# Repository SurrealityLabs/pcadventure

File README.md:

# pcadventure
Adventures in PC Hardware. Probably rather expensive.

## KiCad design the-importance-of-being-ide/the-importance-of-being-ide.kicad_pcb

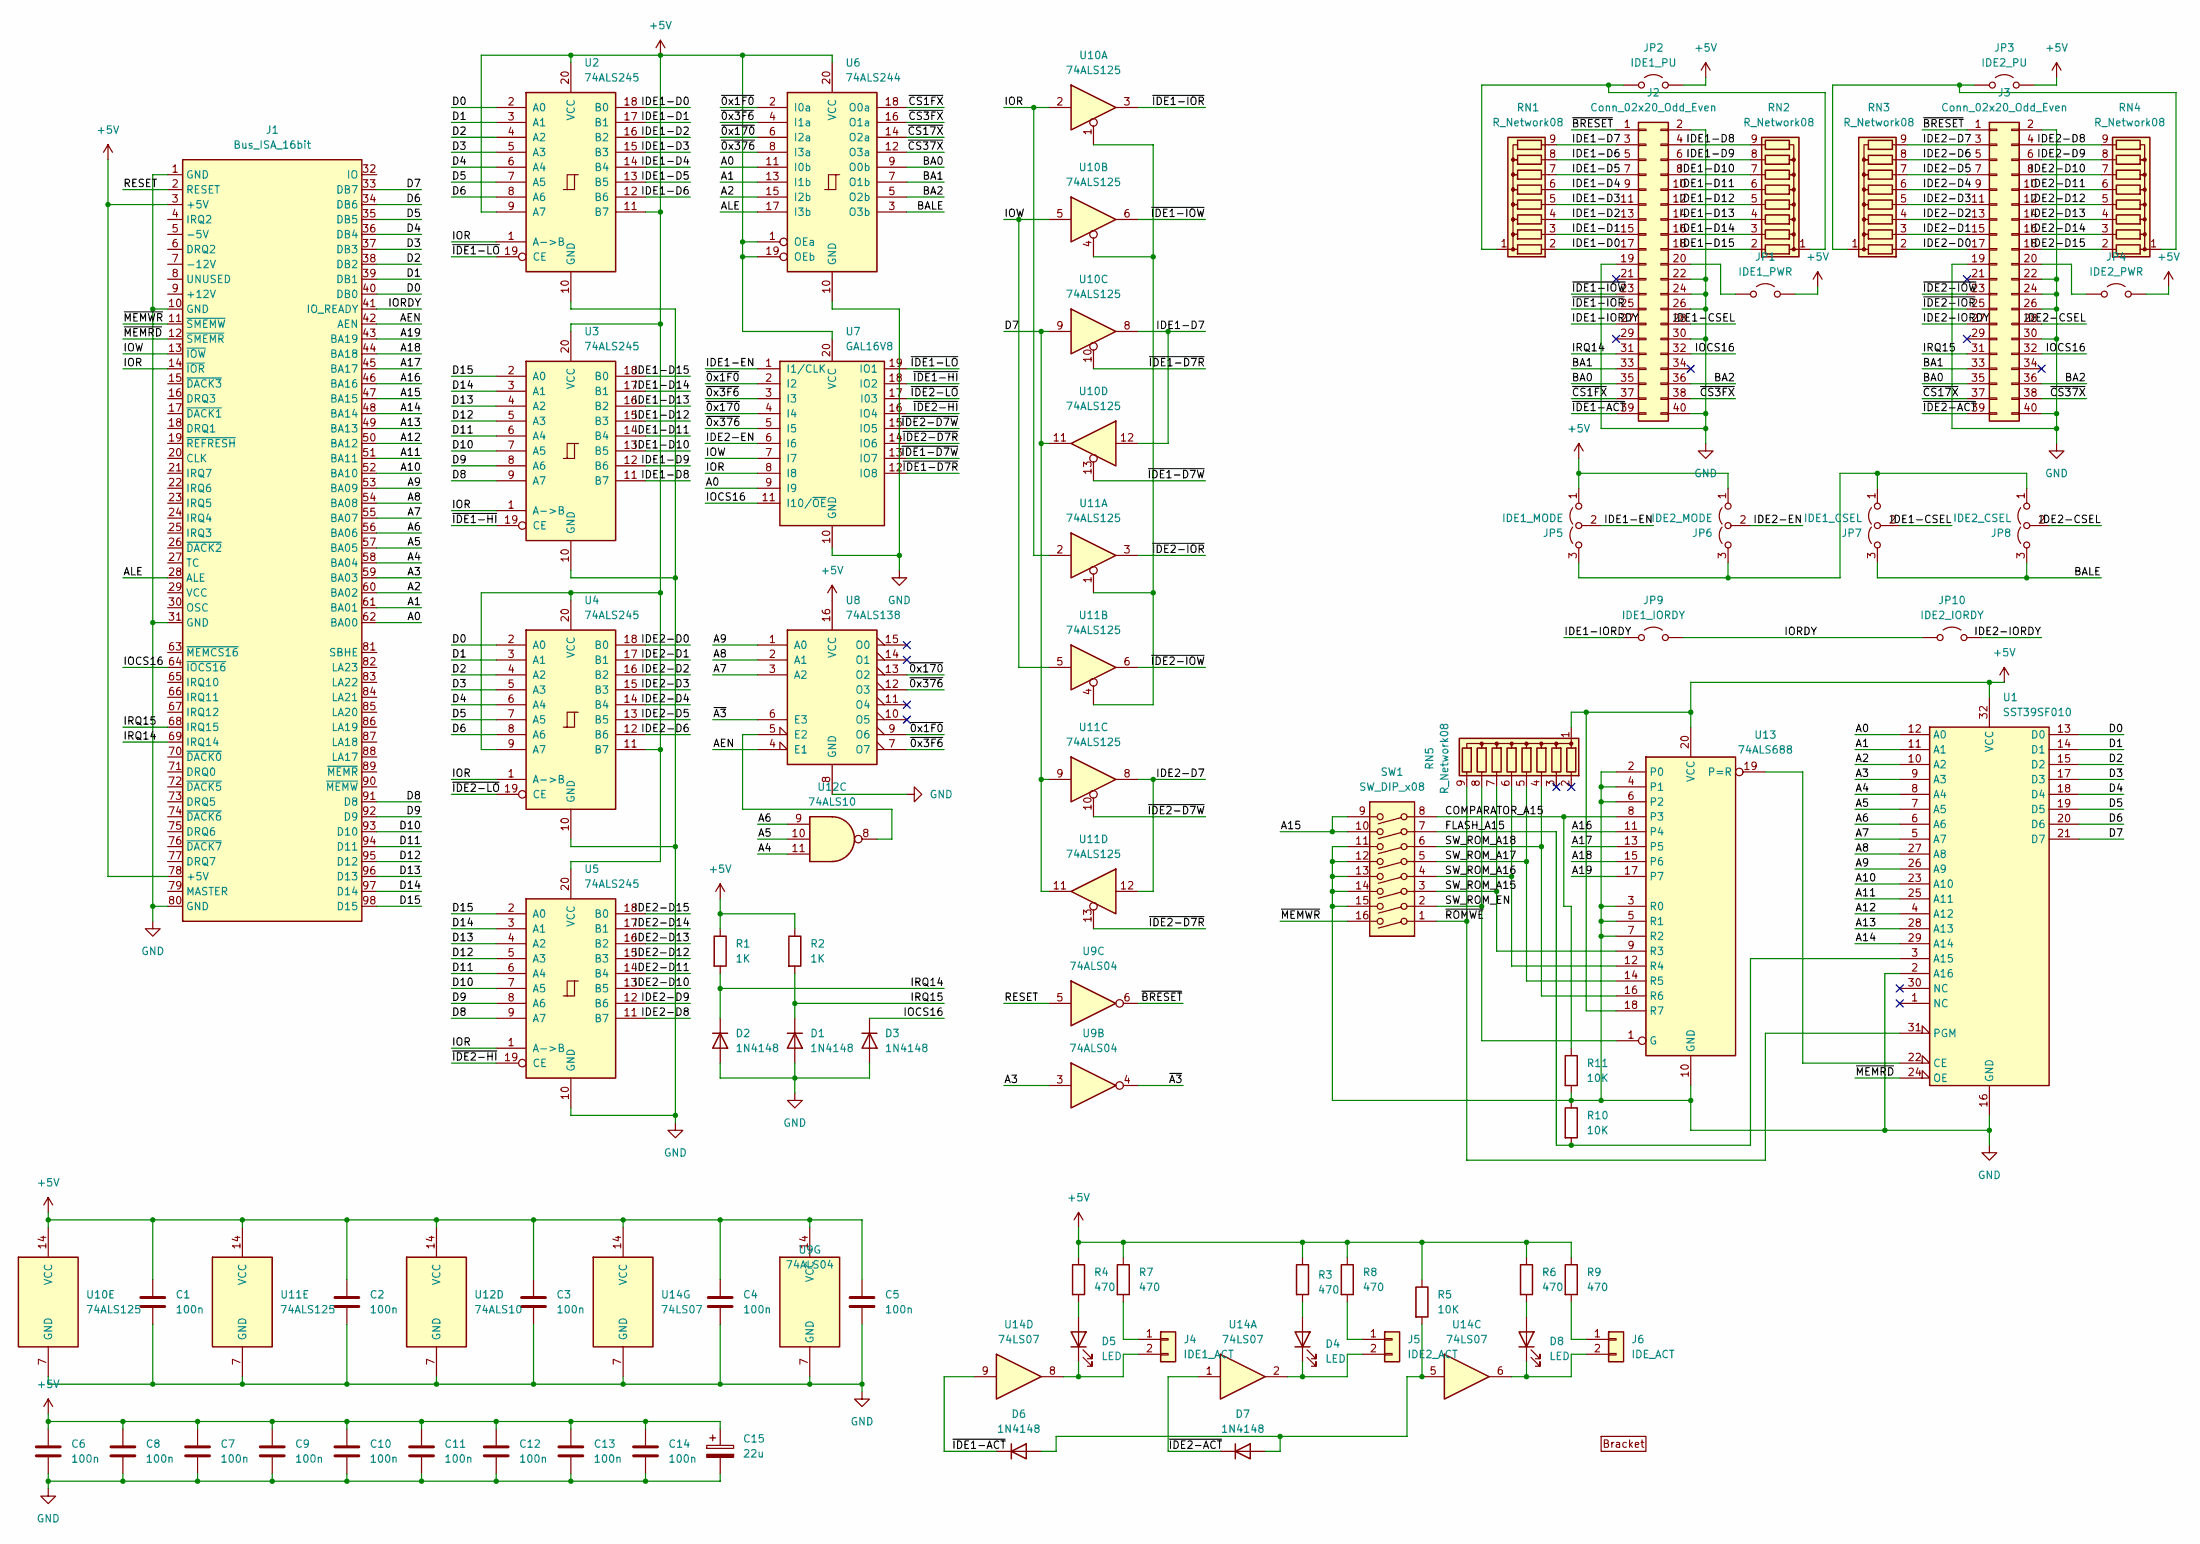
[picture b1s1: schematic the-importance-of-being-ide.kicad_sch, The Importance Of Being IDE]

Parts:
BRACKET1: PC_BRACKET_ISA_KEYSTONE_9202_Rev1
C1, C2, C3, C4, C5, C6, C7, C8, C9, C10, C11, C12, C13, C14: 100n; C_0603_1608Metric_Pad1.08x0.95mm_HandSolder
C15: 22u; CP_Elec_5x5.3
D1, D2, D3, D6, D7: 1N4148; D_SOD-123
D4, D5, D8: LED; LED_0603_1608Metric_Pad1.05x0.95mm_HandSolder
J1: Bus_ISA_16bit; BUS_AT
J2, J3: Conn_02x20_Odd_Even; IDC-Header_2x20_P2.54mm_Vertical
J4: IDE1_ACT; Molex_KK-254_AE-6410-02A_1x02_P2.54mm_Vertical
J5: IDE2_ACT; Molex_KK-254_AE-6410-02A_1x02_P2.54mm_Vertical
J6: IDE_ACT; Molex_KK-254_AE-6410-02A_1x02_P2.54mm_Vertical
JP1: IDE1_PWR; PinHeader_1x02_P2.54mm_Vertical
JP2: IDE1_PU; PinHeader_1x02_P2.54mm_Vertical
JP3: IDE2_PU; PinHeader_1x02_P2.54mm_Vertical
JP4: IDE2_PWR; PinHeader_1x02_P2.54mm_Vertical
JP5: IDE1_MODE; PinHeader_1x03_P2.54mm_Vertical
JP6: IDE2_MODE; PinHeader_1x03_P2.54mm_Vertical
JP7: IDE1_CSEL; PinHeader_1x03_P2.54mm_Vertical
JP8: IDE2_CSEL; PinHeader_1x03_P2.54mm_Vertical
JP9: IDE1_IORDY; PinHeader_1x02_P2.54mm_Vertical
JP10: IDE2_IORDY; PinHeader_1x02_P2.54mm_Vertical
R1, R2: 1K; R_0603_1608Metric_Pad0.98x0.95mm_HandSolder
R3, R4, R6, R7, R8, R9: 470; R_0603_1608Metric_Pad0.98x0.95mm_HandSolder
R5, R10, R11: 10K; R_0603_1608Metric_Pad0.98x0.95mm_HandSolder
RN1, RN2, RN3, RN4, RN5: R_Network08; R_Array_SIP9
SW1: SW_DIP_x08; SW_DIP_SPSTx08_Slide_9.78x22.5mm_W7.62mm_P2.54mm
U1: SST39SF010; DIP-32_W15.24mm
U2, U3, U4, U5: 74ALS245; DIP-20_W7.62mm
U6: 74ALS244; DIP-20_W7.62mm
U7: GAL16V8; DIP-20_W7.62mm
U8: 74ALS138; DIP-16_W7.62mm
U9: 74ALS04; DIP-14_W7.62mm
U10, U11: 74ALS125; DIP-14_W7.62mm
U12: 74ALS10; DIP-14_W7.62mm
U13: 74ALS688; DIP-20_W7.62mm
U14: 74LS07; DIP-14_W7.62mm

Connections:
+5V: C1.1, C2.1, C3.1, C4.1, C5.1, C6.1, C7.1, C8.1, C9.1, C10.1, C11.1, C12.1, C13.1, C14.1, C15.1, J1.3 (+5V), J1.78 (+5V), JP1.2 (B), JP2.2 (B), JP3.2 (B), JP4.2 (B), JP5.1 (A), JP6.1 (A), R1.1, R2.1, R3.1, R4.1, R5.1, R6.1, R7.1, R8.1, R9.1, RN5.1 (common), U1.32 (VCC), U2.9 (A7), U2.11 (B7), U2.20 (VCC), U3.20 (VCC), U4.9 (A7), U4.11 (B7), U4.20 (VCC), U5.20 (VCC), U6.1 (OEa), U6.19 (OEb), U6.20 (VCC), U7.20 (VCC), U8.16 (VCC), U9.14 (VCC), U10.14 (VCC), U11.14 (VCC), U12.14 (VCC), U13.18 (R7), U13.20 (VCC), U14.14 (VCC)
/A0: J1.62 (BA00), U1.12 (A0), U6.11 (I0b), U7.9 (I9)
/A1: J1.61 (BA01), U1.11 (A1), U6.13 (I1b)
/A2: J1.60 (BA02), U1.10 (A2), U6.15 (I2b)
/A3: J1.59 (BA03), U1.9 (A3), U9.3
/A4: J1.58 (BA04), U1.8 (A4), U12.11
/A5: J1.57 (BA05), U1.7 (A5), U12.10
/A6: J1.56 (BA06), U1.6 (A6), U12.9
/A7: J1.55 (BA07), U1.5 (A7), U8.3 (A2)
/A8: J1.54 (BA08), U1.27 (A8), U8.2 (A1)
/A9: J1.53 (BA09), U1.26 (A9), U8.1 (A0)
/A10: J1.52 (BA10), U1.23 (A10)
/A11: J1.51 (BA11), U1.25 (A11)
/A12: J1.50 (BA12), U1.4 (A12)
/A13: J1.49 (BA13), U1.28 (A13)
/A14: J1.48 (BA14), U1.29 (A14)
/A15: J1.47 (BA15), SW1.9, SW1.10
/A16: J1.46 (BA16), U13.11 (P4)
/A17: J1.45 (BA17), U13.13 (P5)
/A18: J1.44 (BA18), U13.15 (P6)
/A19: J1.43 (BA19), U13.17 (P7)
/AEN: J1.42 (AEN), U8.4 (E1)
/ALE: J1.28 (ALE), U6.17 (I3b)
/BA0: J2.35, J3.35, U6.9 (O0b)
/BA1: J2.33, J3.33, U6.7 (O1b)
/BA2: J2.36, J3.36, U6.5 (O2b)
/BALE: JP7.3 (B), JP8.3 (B), U6.3 (O3b)
/COMPARATOR_A15: R11.1, SW1.8, U13.8 (P3)
/D0: J1.40 (DB0), U1.13 (D0), U2.2 (A0), U4.2 (A0)
/D1: J1.39 (DB1), U1.14 (D1), U2.3 (A1), U4.3 (A1)
/D2: J1.38 (DB2), U1.15 (D2), U2.4 (A2), U4.4 (A2)
/D3: J1.37 (DB3), U1.17 (D3), U2.5 (A3), U4.5 (A3)
/D4: J1.36 (DB4), U1.18 (D4), U2.6 (A4), U4.6 (A4)
/D5: J1.35 (DB5), U1.19 (D5), U2.7 (A5), U4.7 (A5)
/D6: J1.34 (DB6), U1.20 (D6), U2.8 (A6), U4.8 (A6)
/D7: J1.33 (DB7), U1.21 (D7), U10.9, U10.11, U11.9, U11.11
/D8: J1.91 (D8), U3.9 (A7), U5.9 (A7)
/D9: J1.92 (D9), U3.8 (A6), U5.8 (A6)
/D10: J1.93 (D10), U3.7 (A5), U5.7 (A5)
/D11: J1.94 (D11), U3.6 (A4), U5.6 (A4)
/D12: J1.95 (D12), U3.5 (A3), U5.5 (A3)
/D13: J1.96 (D13), U3.4 (A2), U5.4 (A2)
/D14: J1.97 (D14), U3.3 (A1), U5.3 (A1)
/D15: J1.98 (D15), U3.2 (A0), U5.2 (A0)
/FLASH_A15: R10.2, SW1.7, U1.3 (A15)
/IDE1-CSEL: J2.28, JP7.2 (C)
/IDE1-D0: J2.17, RN1.2 (R1), U2.18 (B0)
/IDE1-D1: J2.15, RN1.3 (R2), U2.17 (B1)
/IDE1-D2: J2.13, RN1.4 (R3), U2.16 (B2)
/IDE1-D3: J2.11, RN1.5 (R4), U2.15 (B3)
/IDE1-D4: J2.9, RN1.6 (R5), U2.14 (B4)
/IDE1-D5: J2.7, RN1.7 (R6), U2.13 (B5)
/IDE1-D6: J2.5, RN1.8 (R7), U2.12 (B6)
/IDE1-D7: J2.3, RN1.9 (R8), U10.8, U10.12
/IDE1-D8: J2.4, RN2.9 (R8), U3.11 (B7)
/IDE1-D9: J2.6, RN2.8 (R7), U3.12 (B6)
/IDE1-D10: J2.8, RN2.7 (R6), U3.13 (B5)
/IDE1-D11: J2.10, RN2.6 (R5), U3.14 (B4)
/IDE1-D12: J2.12, RN2.5 (R4), U3.15 (B3)
/IDE1-D13: J2.14, RN2.4 (R3), U3.16 (B2)
/IDE1-D14: J2.16, RN2.3 (R2), U3.17 (B1)
/IDE1-D15: J2.18, RN2.2 (R1), U3.18 (B0)
/IDE1-EN: JP5.2 (C), U7.1 (I1/CLK)
/IDE1-IORDY: J2.27, JP9.1 (A)
/IDE2-CSEL: J3.28, JP8.2 (C)
/IDE2-D0: J3.17, RN3.2 (R1), U4.18 (B0)
/IDE2-D1: J3.15, RN3.3 (R2), U4.17 (B1)
/IDE2-D2: J3.13, RN3.4 (R3), U4.16 (B2)
/IDE2-D3: J3.11, RN3.5 (R4), U4.15 (B3)
/IDE2-D4: J3.9, RN3.6 (R5), U4.14 (B4)
/IDE2-D5: J3.7, RN3.7 (R6), U4.13 (B5)
/IDE2-D6: J3.5, RN3.8 (R7), U4.12 (B6)
/IDE2-D7: J3.3, RN3.9 (R8), U11.8, U11.12
/IDE2-D8: J3.4, RN4.9 (R8), U5.11 (B7)
/IDE2-D9: J3.6, RN4.8 (R7), U5.12 (B6)
/IDE2-D10: J3.8, RN4.7 (R6), U5.13 (B5)
/IDE2-D11: J3.10, RN4.6 (R5), U5.14 (B4)
/IDE2-D12: J3.12, RN4.5 (R4), U5.15 (B3)
/IDE2-D13: J3.14, RN4.4 (R3), U5.16 (B2)
/IDE2-D14: J3.16, RN4.3 (R2), U5.17 (B1)
/IDE2-D15: J3.18, RN4.2 (R1), U5.18 (B0)
/IDE2-EN: JP6.2 (C), U7.6 (I6)
/IDE2-IORDY: J3.27, JP10.1 (A)
/IOCS16: D3.1 (K), J1.64 (~IOCS16), J2.32, J3.32, U7.11 (I10/~OE)
/IOR: J1.14 (~IOR), U2.1 (A->B), U3.1 (A->B), U4.1 (A->B), U5.1 (A->B), U7.8 (I8), U10.2, U11.2
/IORDY: J1.41 (IO_READY), JP9.2 (B), JP10.2 (B)
/IOW: J1.13 (~IOW), U7.7 (I7), U10.5, U11.5
/IRQ14: D2.1 (K), J1.69 (IRQ14), J2.31, R1.2
/IRQ15: D1.1 (K), J1.68 (IRQ15), J3.31, R2.2
/RESET: J1.2 (RESET), U9.5
/SW_ROM_A15: RN5.7 (R6), SW1.3, U13.9 (R3)
/SW_ROM_A16: RN5.6 (R5), SW1.4, U13.12 (R4)
/SW_ROM_A17: RN5.5 (R4), SW1.5, U13.14 (R5)
/SW_ROM_A18: RN5.4 (R3), SW1.6, U13.16 (R6)
/SW_ROM_EN: RN5.8 (R7), SW1.2, U13.1 (G)
/~0x1F0: U6.2 (I0a), U7.2 (I2), U8.9 (O6)
/~0x3F6: U6.4 (I1a), U7.3 (I3), U8.7 (O7)
/~0x170: U6.6 (I2a), U7.4 (I4), U8.13 (O2)
/~0x376: U6.8 (I3a), U7.5 (I5), U8.12 (O3)
/~A3: U8.6 (E3), U9.4
/~BRESET: J2.1, J3.1, U9.6
/~CS1FX: J2.37, U6.18 (O0a)
/~CS3FX: J2.38, U6.16 (O1a)
/~CS17X: J3.37, U6.14 (O2a)
/~CS37X: J3.38, U6.12 (O3a)
/~IDE1-ACT: D6.1 (K), J2.39, U14.9
/~IDE1-D7R: U7.12 (IO8), U10.10
/~IDE1-D7W: U7.13 (IO7), U10.13
/~IDE1-HI: U3.19 (CE), U7.18 (IO2)
/~IDE1-IOR: J2.25, U10.3
/~IDE1-IOW: J2.23, U10.6
/~IDE1-LO: U2.19 (CE), U7.19 (IO1)
/~IDE2-ACT: D7.1 (K), J3.39, U14.1
/~IDE2-D7R: U7.14 (IO6), U11.13
/~IDE2-D7W: U7.15 (IO5), U11.10
/~IDE2-HI: U5.19 (CE), U7.16 (IO4)
/~IDE2-IOR: J3.25, U11.3
/~IDE2-IOW: J3.23, U11.6
/~IDE2-LO: U4.19 (CE), U7.17 (I03)
/~MEMRD: J1.12 (~SMEMR), U1.24 (OE)
/~MEMWR: J1.11 (~SMEMW), SW1.16
/~ROMWE: RN5.9 (R8), SW1.1, U1.31 (PGM)
GND: C1.2, C2.2, C3.2, C4.2, C5.2, C6.2, C7.2, C8.2, C9.2, C10.2, C11.2, C12.2, C13.2, C14.2, C15.2, D1.2 (A), D2.2 (A), D3.2 (A), J1.1 (GND), J1.10 (GND), J1.31 (GND), J1.80 (GND), J2.2, J2.19, J2.22, J2.24, J2.26, J2.30, J2.40, J3.2, J3.19, J3.22, J3.24, J3.26, J3.30, J3.40, R10.1, R11.2, SW1.11, SW1.12, SW1.13, SW1.14, SW1.15, U1.2 (A16), U1.16 (GND), U2.10 (GND), U3.10 (GND), U4.10 (GND), U5.10 (GND), U6.10 (GND), U7.10 (GND), U8.8 (GND), U9.7 (GND), U10.7 (GND), U11.7 (GND), U12.7 (GND), U13.2 (P0), U13.3 (R0), U13.4 (P1), U13.5 (R1), U13.6 (P2), U13.7 (R2), U13.10 (GND), U14.7 (GND)
unnamed: D4.2 (A), R3.2
unnamed: D4.1 (K), J5.2, U14.2
unnamed: D5.2 (A), R4.2
unnamed: D5.1 (K), J4.2, U14.8
unnamed: D6.2 (A), D7.2 (A), R5.2, U14.5
unnamed: D8.2 (A), R6.2
unnamed: D8.1 (K), J6.2, U14.6
unnamed: J2.20, JP1.1 (A)
unnamed: J3.20, JP4.1 (A)
unnamed: J4.1, R7.2
unnamed: J5.1, R8.2
unnamed: J6.1, R9.2
unnamed: JP2.1 (A), RN1.1 (common), RN2.1 (common)
unnamed: JP3.1 (A), RN3.1 (common), RN4.1 (common)
unnamed: JP5.3 (B), JP6.3 (B), JP7.1 (A), JP8.1 (A)
unnamed: U1.22 (CE), U13.19 (P=R)
unnamed: U8.5 (E2), U12.8
unnamed: U10.1, U10.4, U11.1, U11.4

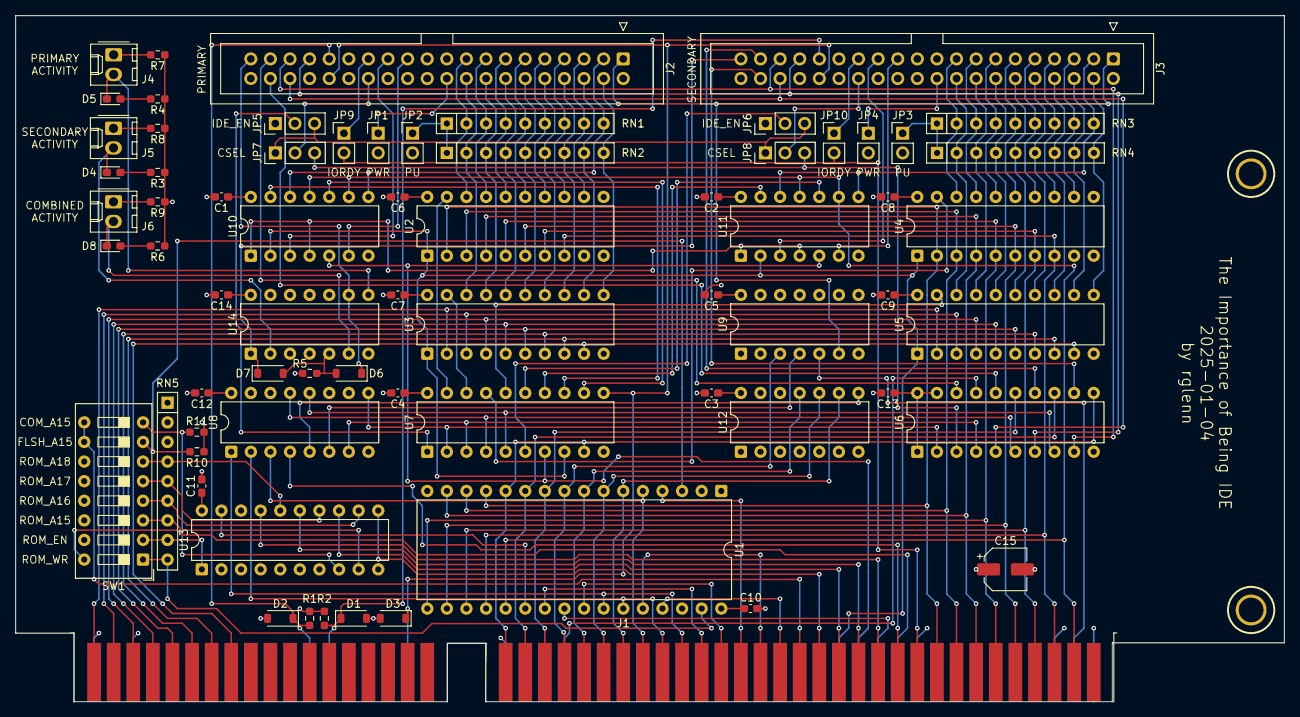
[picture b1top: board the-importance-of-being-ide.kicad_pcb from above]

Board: 4 copper layers, 164.4 x 88.9 mm, 71 parts (0 on the bottom side), 141 nets.

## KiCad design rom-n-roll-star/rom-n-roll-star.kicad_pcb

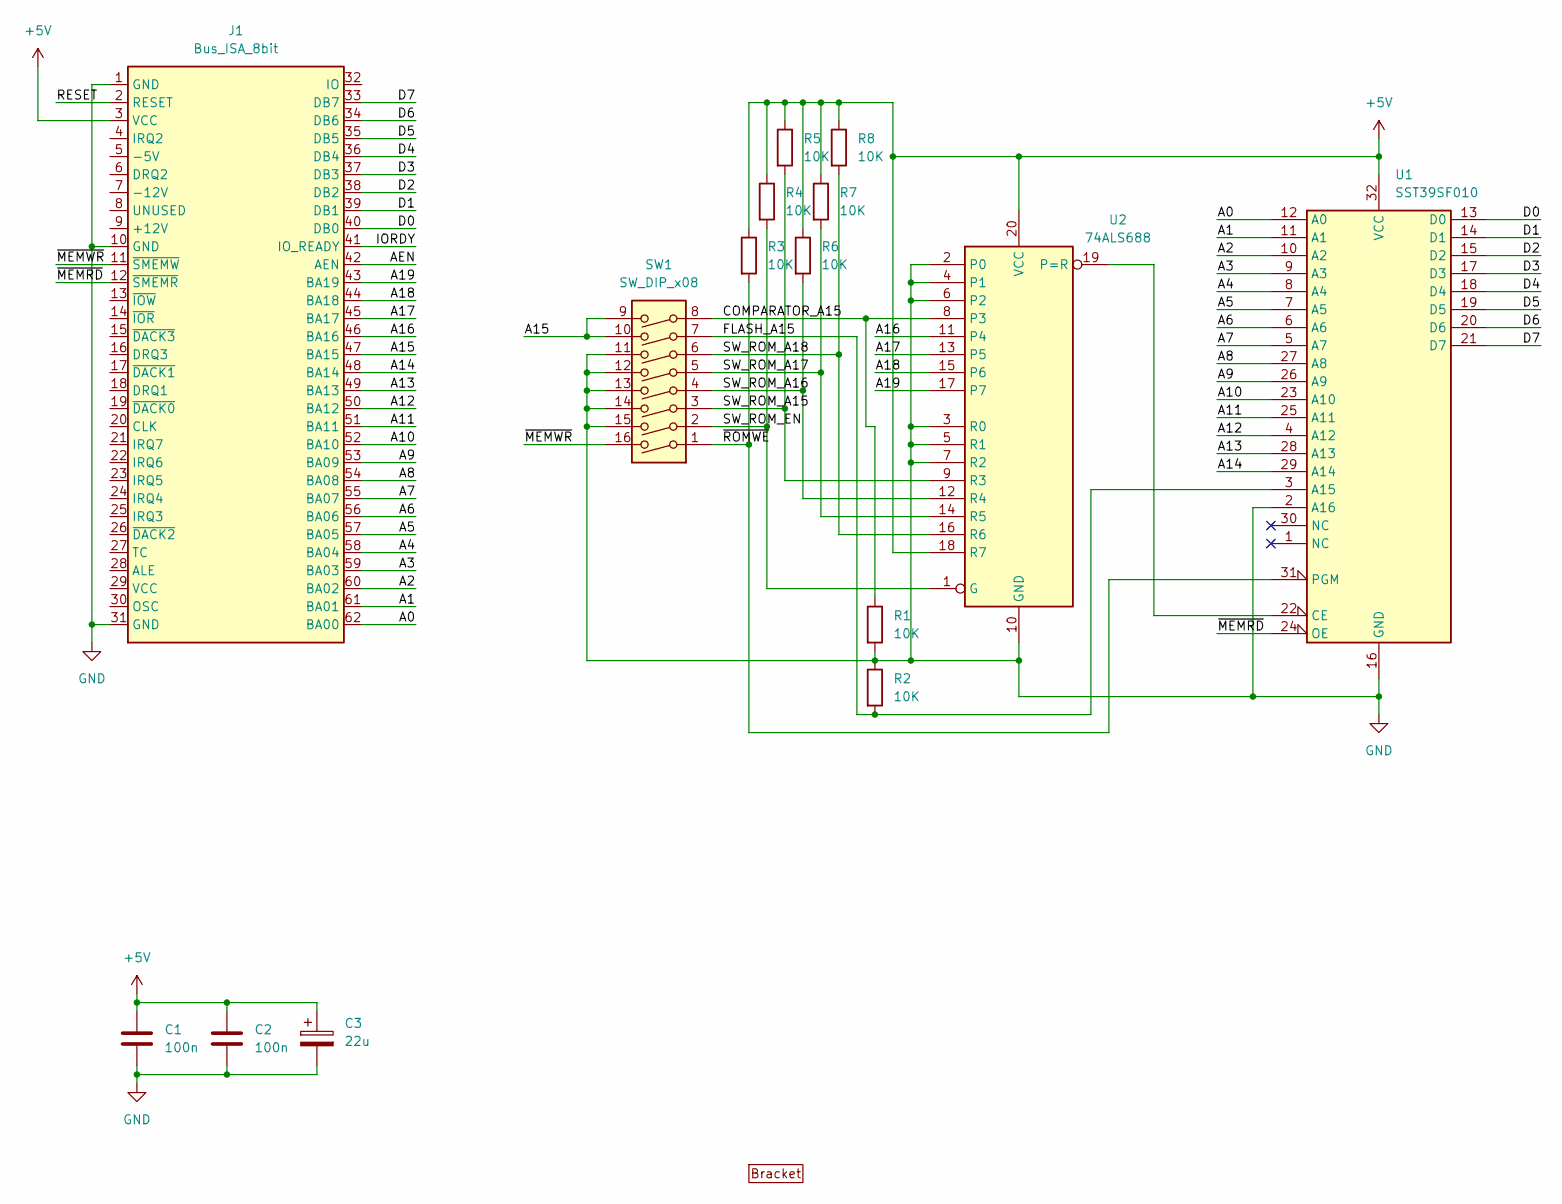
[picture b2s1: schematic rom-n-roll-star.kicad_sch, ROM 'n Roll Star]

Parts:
BRACKET1: PC_BRACKET_ISA_KEYSTONE_9202_Rev1
C1, C2: 100n; C_0603_1608Metric_Pad1.08x0.95mm_HandSolder
C3: 22u; CP_Elec_5x5.3
J1: Bus_ISA_8bit; BUS_AT_8BIT
R1, R2, R3, R4, R5, R6, R7, R8: 10K; R_0603_1608Metric_Pad0.98x0.95mm_HandSolder
SW1: SW_DIP_x08; SW_DIP_SPSTx08_Slide_9.78x22.5mm_W7.62mm_P2.54mm
U1: SST39SF010; DIP-32_W15.24mm
U2: 74ALS688; DIP-20_W7.62mm

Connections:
+5V: C1.1, C2.1, C3.1, J1.3 (VCC), R3.1, R4.1, R5.1, R6.1, R7.1, R8.1, U1.32 (VCC), U2.18 (R7), U2.20 (VCC)
/A0: J1.62 (BA00), U1.12 (A0)
/A1: J1.61 (BA01), U1.11 (A1)
/A2: J1.60 (BA02), U1.10 (A2)
/A3: J1.59 (BA03), U1.9 (A3)
/A4: J1.58 (BA04), U1.8 (A4)
/A5: J1.57 (BA05), U1.7 (A5)
/A6: J1.56 (BA06), U1.6 (A6)
/A7: J1.55 (BA07), U1.5 (A7)
/A8: J1.54 (BA08), U1.27 (A8)
/A9: J1.53 (BA09), U1.26 (A9)
/A10: J1.52 (BA10), U1.23 (A10)
/A11: J1.51 (BA11), U1.25 (A11)
/A12: J1.50 (BA12), U1.4 (A12)
/A13: J1.49 (BA13), U1.28 (A13)
/A14: J1.48 (BA14), U1.29 (A14)
/A15: J1.47 (BA15), SW1.9, SW1.10
/A16: J1.46 (BA16), U2.11 (P4)
/A17: J1.45 (BA17), U2.13 (P5)
/A18: J1.44 (BA18), U2.15 (P6)
/A19: J1.43 (BA19), U2.17 (P7)
/AEN: J1.42 (AEN)
/COMPARATOR_A15: R1.1, SW1.8, U2.8 (P3)
/D0: J1.40 (DB0), U1.13 (D0)
/D1: J1.39 (DB1), U1.14 (D1)
/D2: J1.38 (DB2), U1.15 (D2)
/D3: J1.37 (DB3), U1.17 (D3)
/D4: J1.36 (DB4), U1.18 (D4)
/D5: J1.35 (DB5), U1.19 (D5)
/D6: J1.34 (DB6), U1.20 (D6)
/D7: J1.33 (DB7), U1.21 (D7)
/FLASH_A15: R2.2, SW1.7, U1.3 (A15)
/IORDY: J1.41 (IO_READY)
/RESET: J1.2 (RESET)
/SW_ROM_A15: R5.2, SW1.3, U2.9 (R3)
/SW_ROM_A16: R6.2, SW1.4, U2.12 (R4)
/SW_ROM_A17: R7.2, SW1.5, U2.14 (R5)
/SW_ROM_A18: R8.2, SW1.6, U2.16 (R6)
/SW_ROM_EN: R4.2, SW1.2, U2.1 (G)
/~MEMRD: J1.12 (~SMEMR), U1.24 (OE)
/~MEMWR: J1.11 (~SMEMW), SW1.16
/~ROMWE: R3.2, SW1.1, U1.31 (PGM)
GND: C1.2, C2.2, C3.2, J1.1 (GND), J1.10 (GND), J1.31 (GND), R1.2, R2.1, SW1.11, SW1.12, SW1.13, SW1.14, SW1.15, U1.2 (A16), U1.16 (GND), U2.2 (P0), U2.3 (R0), U2.4 (P1), U2.5 (R1), U2.6 (P2), U2.7 (R2), U2.10 (GND)
unnamed: U1.22 (CE), U2.19 (P=R)

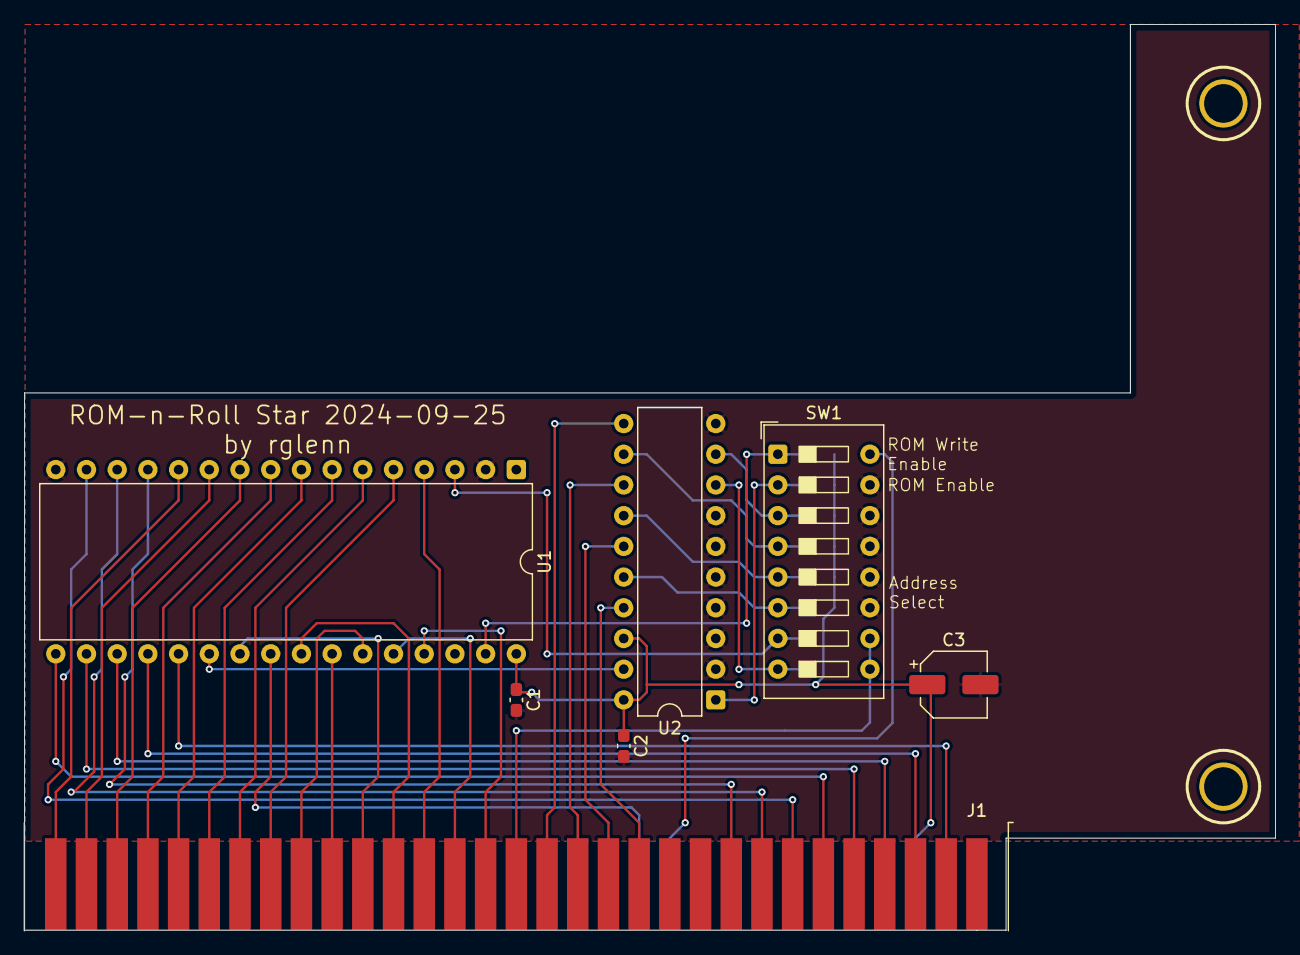
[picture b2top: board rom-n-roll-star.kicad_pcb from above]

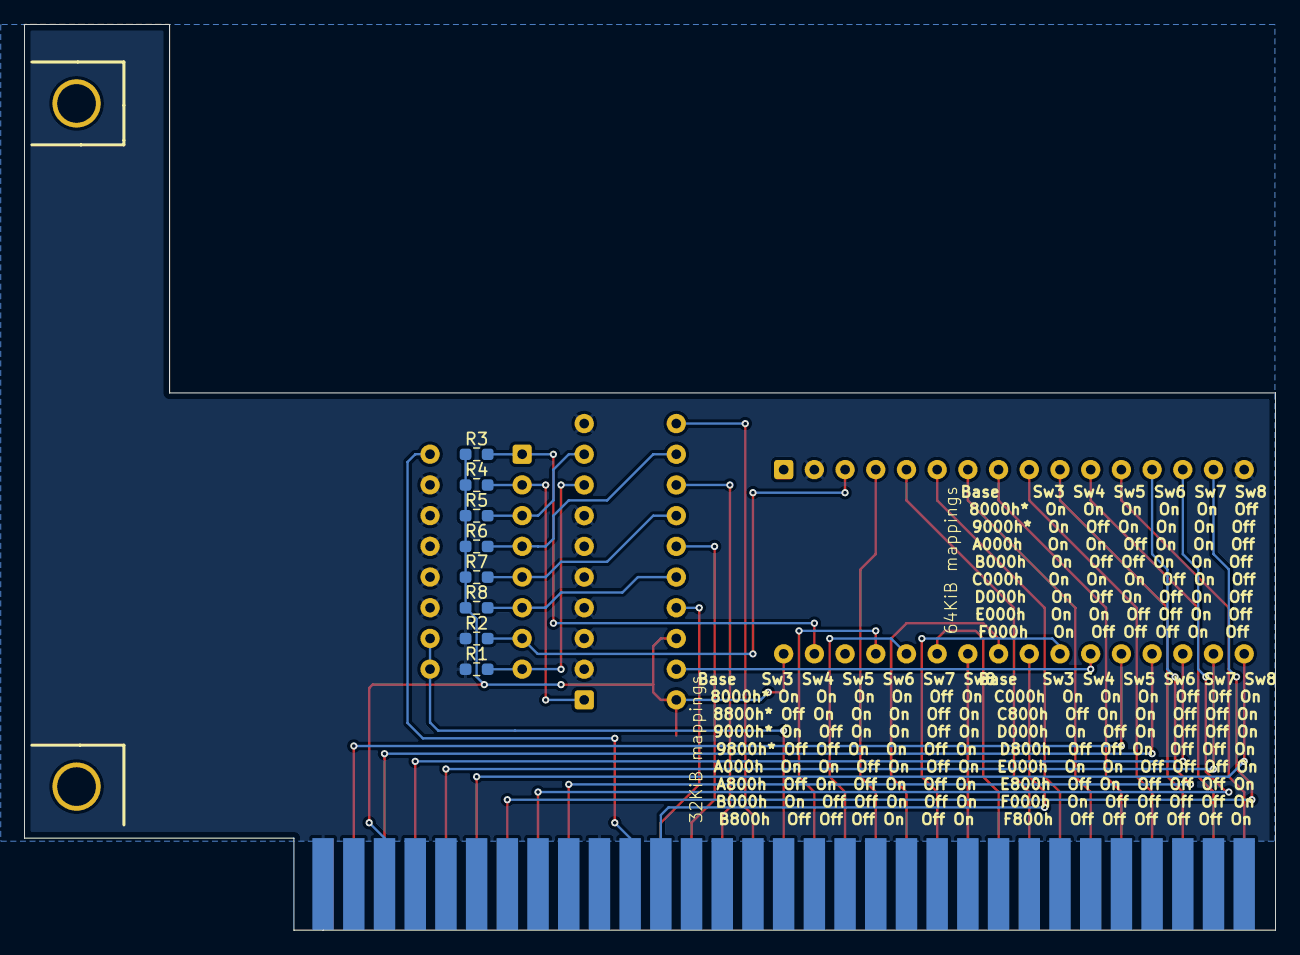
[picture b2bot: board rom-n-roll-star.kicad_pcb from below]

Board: 2 copper layers, 103.5 x 74.9 mm, 16 parts (8 on the bottom side), 41 nets.

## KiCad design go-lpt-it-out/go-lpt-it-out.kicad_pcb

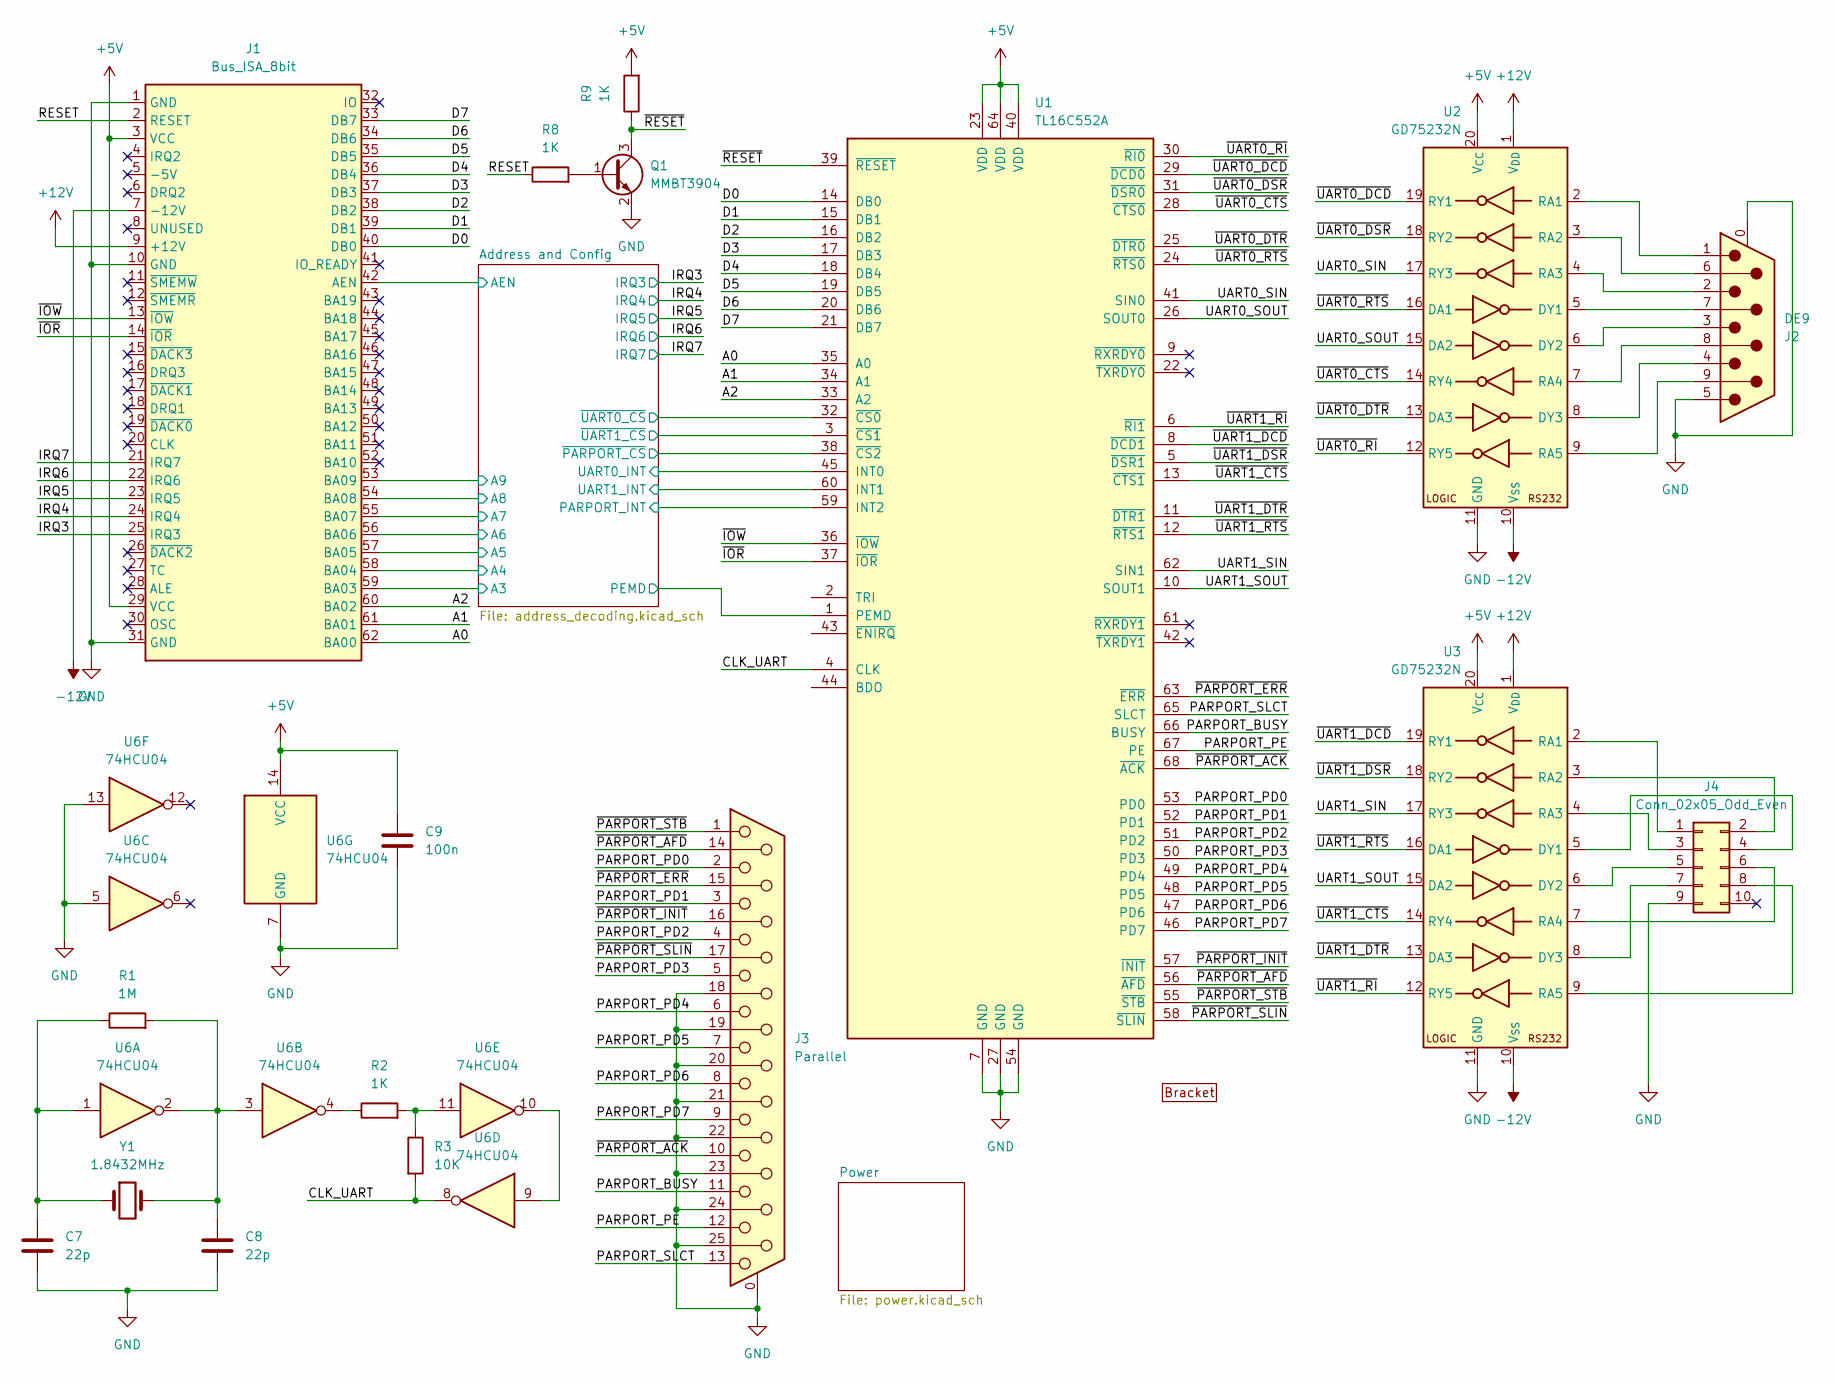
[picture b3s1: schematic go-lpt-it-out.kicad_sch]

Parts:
BRACKET1: PC_BRACKET_ISA_KEYSTONE_9200_Rev1_1
C7, C8: 22p; C_0603_1608Metric_Pad1.08x0.95mm_HandSolder
C9: 100n; C_0603_1608Metric_Pad1.08x0.95mm_HandSolder
J1: Bus_ISA_8bit; BUS_AT_8BIT
J2: DE9; DSUB-9_Pins_Horizontal_P2.77x2.84mm_EdgePinOffset7.70mm_Hou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
J3: Parallel; DSUB-25_Socket_Horizontal_P2.77x2.84mm_EdgePinOffset7.70mm_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
J4: Conn_02x05_Odd_Even; IDC-Header_2x05_P2.54mm_Vertical
Q1: MMBT3904; SOT-23
R1: 1M; R_0603_1608Metric_Pad0.98x0.95mm_HandSolder
R2, R8, R9: 1K; R_0603_1608Metric_Pad0.98x0.95mm_HandSolder
R3: 10K; R_0603_1608Metric_Pad0.98x0.95mm_HandSolder
U1: TL16C552A; PLCC-68_THT-Socket
U2, U3: GD75232N; DIP-20_W7.62mm
U6: 74HCU04; SO-14_3.9x8.65mm_P1.27mm
Y1: 1.8432MHz; Crystal_HC49-U_Vertical

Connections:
+5V: C9.1, J1.3 (VCC), J1.29 (VCC), R9.2, U1.23 (VDD), U1.40 (VDD), U1.64 (VDD), U2.20 (V_{CC}), U3.20 (V_{CC}), U6.14 (VCC); also elsewhere on the board
+12V: J1.9 (+12V), U2.1 (V_{DD}), U3.1 (V_{DD}); also elsewhere on the board
-12V: J1.7 (-12V), U2.10 (V_{SS}), U3.10 (V_{SS}); also elsewhere on the board
/A0: J1.62 (BA00), U1.35 (A0)
/A1: J1.61 (BA01), U1.34 (A1)
/A2: J1.60 (BA02), U1.33 (A2)
/Address and Config/A3: J1.59 (BA03); also elsewhere on the board
/Address and Config/A4: J1.58 (BA04); also elsewhere on the board
/Address and Config/A5: J1.57 (BA05); also elsewhere on the board
/Address and Config/A6: J1.56 (BA06); also elsewhere on the board
/Address and Config/A7: J1.55 (BA07); also elsewhere on the board
/Address and Config/A8: J1.54 (BA08); also elsewhere on the board
/Address and Config/A9: J1.53 (BA09); also elsewhere on the board
/Address and Config/AEN: J1.42 (AEN); also elsewhere on the board
/Address and Config/PARPORT_INT: U1.59 (INT2); also elsewhere on the board
/Address and Config/PEMD: U1.1 (PEMD); also elsewhere on the board
/Address and Config/UART0_INT: U1.45 (INT0); also elsewhere on the board
/Address and Config/UART1_INT: U1.60 (INT1); also elsewhere on the board
/Address and Config/~PARPORT_CS: U1.38 (~CS2); also elsewhere on the board
/Address and Config/~UART0_CS: U1.32 (~CS0); also elsewhere on the board
/Address and Config/~UART1_CS: U1.3 (~CS1); also elsewhere on the board
/CLK_UART: R3.2, U1.4 (CLK), U6.8
/D0: J1.40 (DB0), U1.14 (DB0)
/D1: J1.39 (DB1), U1.15 (DB1)
/D2: J1.38 (DB2), U1.16 (DB2)
/D3: J1.37 (DB3), U1.17 (DB3)
/D4: J1.36 (DB4), U1.18 (DB4)
/D5: J1.35 (DB5), U1.19 (DB5)
/D6: J1.34 (DB6), U1.20 (DB6)
/D7: J1.33 (DB7), U1.21 (DB7)
/IRQ3: J1.25 (IRQ3); also elsewhere on the board
/IRQ4: J1.24 (IRQ4); also elsewhere on the board
/IRQ5: J1.23 (IRQ5); also elsewhere on the board
/IRQ6: J1.22 (IRQ6); also elsewhere on the board
/IRQ7: J1.21 (IRQ7); also elsewhere on the board
/PARPORT_BUSY: J3.11, U1.66 (BUSY)
/PARPORT_PD0: J3.2, U1.53 (PD0)
/PARPORT_PD1: J3.3, U1.52 (PD1)
/PARPORT_PD2: J3.4, U1.51 (PD2)
/PARPORT_PD3: J3.5, U1.50 (PD3)
/PARPORT_PD4: J3.6, U1.49 (PD4)
/PARPORT_PD5: J3.7, U1.48 (PD5)
/PARPORT_PD6: J3.8, U1.47 (PD6)
/PARPORT_PD7: J3.9, U1.46 (PD7)
/PARPORT_PE: J3.12, U1.67 (PE)
/PARPORT_SLCT: J3.13, U1.65 (SLCT)
/RESET: J1.2 (RESET), R8.1
/UART0_SIN: U1.41 (SIN0), U2.17 (RY3)
/UART0_SOUT: U1.26 (SOUT0), U2.15 (DA2)
/UART1_SIN: U1.62 (SIN1), U3.17 (RY3)
/UART1_SOUT: U1.10 (SOUT1), U3.15 (DA2)
/~IOR: J1.14 (~IOR), U1.37 (~IOR)
/~IOW: J1.13 (~IOW), U1.36 (~IOW)
/~PARPORT_ACK: J3.10, U1.68 (~ACK)
/~PARPORT_AFD: J3.14, U1.56 (~AFD)
/~PARPORT_ERR: J3.15, U1.63 (~ERR)
/~PARPORT_INIT: J3.16, U1.57 (~INIT)
/~PARPORT_SLIN: J3.17, U1.58 (~SLIN)
/~PARPORT_STB: J3.1, U1.55 (~STB)
/~RESET: Q1.3 (C), R9.1, U1.39 (~RESET)
/~UART0_CTS: U1.28 (~CTS0), U2.14 (RY4)
/~UART0_DCD: U1.29 (~DCD0), U2.19 (RY1)
/~UART0_DSR: U1.31 (~DSR0), U2.18 (RY2)
/~UART0_DTR: U1.25 (~DTR0), U2.13 (DA3)
/~UART0_RI: U1.30 (~RI0), U2.12 (RY5)
/~UART0_RTS: U1.24 (~RTS0), U2.16 (DA1)
/~UART1_CTS: U1.13 (~CTS1), U3.14 (RY4)
/~UART1_DCD: U1.8 (~DCD1), U3.19 (RY1)
/~UART1_DSR: U1.5 (~DSR1), U3.18 (RY2)
/~UART1_DTR: U1.11 (~DTR1), U3.13 (DA3)
/~UART1_RI: U1.6 (~RI1), U3.12 (RY5)
/~UART1_RTS: U1.12 (~RTS1), U3.16 (DA1)
GND: C7.2, C8.2, C9.2, J1.1 (GND), J1.10 (GND), J1.31 (GND), J2.0 (PAD), J2.5, J3.0 (PAD), J3.18, J3.19, J3.20, J3.21, J3.22, J3.23, J3.24, J3.25, J4.9, Q1.2 (E), U1.7 (GND), U1.27 (GND), U1.54 (GND), U2.11 (GND), U3.11 (GND), U6.5, U6.7 (GND), U6.13; also elsewhere on the board
unnamed: C7.1, R1.1, U6.1, Y1.1
unnamed: C8.1, R1.2, U6.2, U6.3, Y1.2
unnamed: J4.1, U3.2 (RA1)
unnamed: J4.2, U3.3 (RA2)
unnamed: J4.3, U3.4 (RA3)
unnamed: J4.4, U3.5 (DY1)
unnamed: J4.5, U3.6 (DY2)
unnamed: J4.6, U3.7 (RA4)
unnamed: J4.7, U3.8 (DY3)
unnamed: J4.8, U3.9 (RA5)
unnamed: Q1.1 (B), R8.2
unnamed: R2.1, U6.4
unnamed: R2.2, R3.1, U6.11
unnamed: J2.7, U2.5 (DY1)
unnamed: J2.3, U2.6 (DY2)
unnamed: J2.4, U2.8 (DY3)
unnamed: J2.1, U2.2 (RA1)
unnamed: J2.6, U2.3 (RA2)
unnamed: J2.2, U2.4 (RA3)
unnamed: J2.8, U2.7 (RA4)
unnamed: J2.9, U2.9 (RA5)
unnamed: U6.9, U6.10
